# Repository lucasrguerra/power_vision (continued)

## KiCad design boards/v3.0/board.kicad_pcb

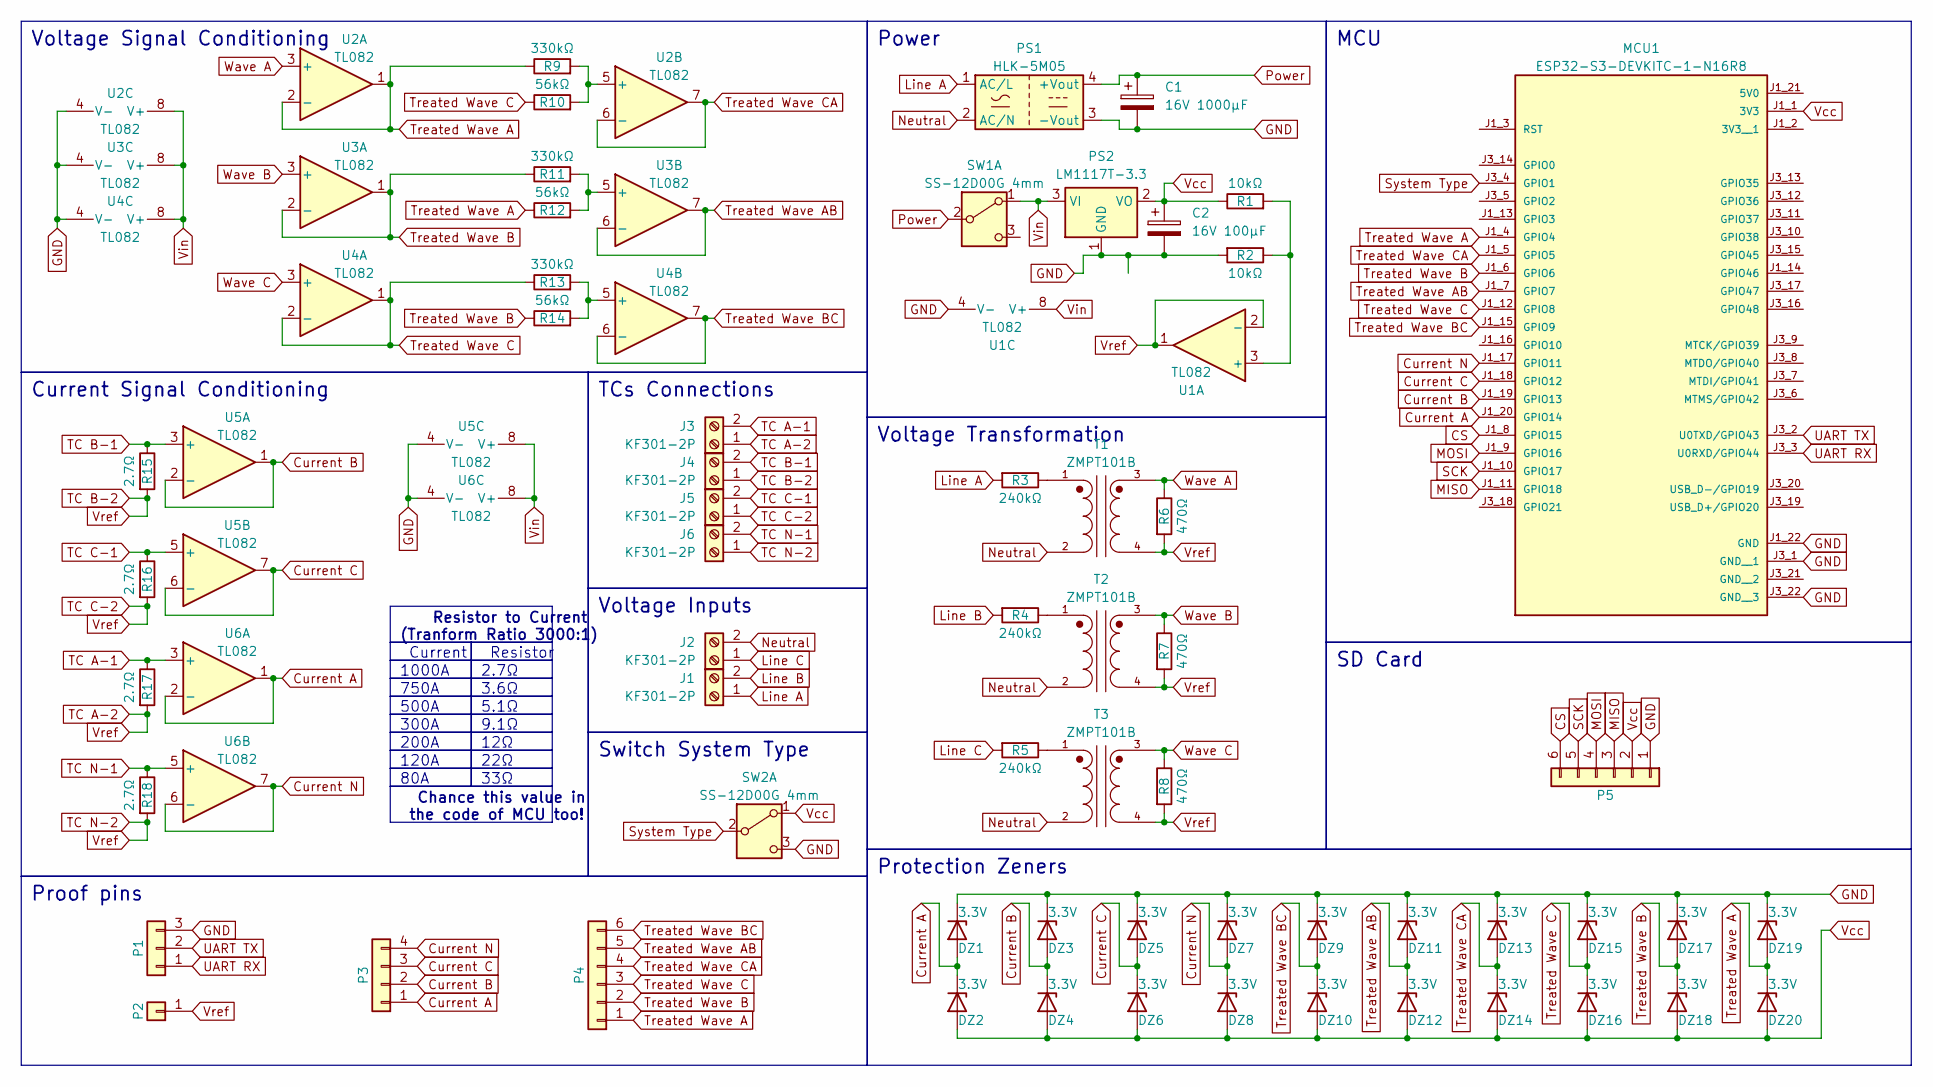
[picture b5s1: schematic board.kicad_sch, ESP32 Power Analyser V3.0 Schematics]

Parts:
C1: 16V 1000µF; CP_Radial_D6.3mm_P2.50mm
C2: 16V 100µF; CP_Radial_D5.0mm_P2.00mm
DZ1, DZ2, DZ3, DZ4, DZ5, DZ6, DZ7, DZ8, DZ9, DZ10, DZ11, DZ12, DZ13, DZ14, DZ15, DZ16, DZ17, DZ18, DZ19, DZ20: 3.3V; D_DO-34_SOD68_P7.62mm_Horizontal
J1, J2, J3, J4, J5, J6: KF301-2P; TerminalBlock_bornier-2_P5.08mm
MCU1: ESP32-S3-DEVKITC-1-N16R8; XCVR_ESP32-S3-DEVKITC-1-N8R2; PARTREV V1
P1: Pin Header; PinHeader_1x03_P2.54mm_Vertical
P2: Pin Header; PinHeader_1x01_P2.54mm_Vertical
P3: Pin Header; PinHeader_1x04_P2.54mm_Vertical
P4, P5: Pin Header; PinHeader_1x06_P2.54mm_Vertical
PS1: HLK-5M05; Converter_ACDC_HiLink_HLK-5Mxx
PS2: LM1117T-3.3; TO-220-3_Vertical
R1, R2: 10kΩ; R_Axial_DIN0207_L6.3mm_D2.5mm_P10.16mm_Horizontal
R3, R4, R5: 240kΩ; R_Axial_DIN0207_L6.3mm_D2.5mm_P10.16mm_Horizontal
R6, R7, R8: 470Ω; R_Axial_DIN0207_L6.3mm_D2.5mm_P10.16mm_Horizontal
R9, R11, R13: 330kΩ; R_Axial_DIN0207_L6.3mm_D2.5mm_P10.16mm_Horizontal
R10, R12, R14: 56kΩ; R_Axial_DIN0207_L6.3mm_D2.5mm_P10.16mm_Horizontal
R15, R16, R17, R18: 2.7Ω; R_Axial_DIN0207_L6.3mm_D2.5mm_P10.16mm_Horizontal
SW1, SW2: SS-12D00G 4mm; PinHeader_1x03_P2.54mm_Vertical
T1, T2, T3: ZMPT101B; XFMR_ZMPT101B; PARTREV NA
U1, U2, U3, U4, U5, U6: TL082; DIP-8_W7.62mm_Socket

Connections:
CS: MCU1.J1_8 (GPIO15), P5.6
Current A: DZ1.2 (A), DZ2.1 (K), MCU1.J1_20 (GPIO14), P3.1, U6.1, U6.2 (-)
Current B: DZ3.2 (A), DZ4.1 (K), MCU1.J1_19 (GPIO13), P3.2, U5.1, U5.2 (-)
Current C: DZ5.2 (A), DZ6.1 (K), MCU1.J1_18 (GPIO12), P3.3, U5.6 (-), U5.7
Current N: DZ7.2 (A), DZ8.1 (K), MCU1.J1_17 (GPIO11), P3.4, U6.6 (-), U6.7
GND: C1.2, C2.2, DZ1.1 (K), DZ3.1 (K), DZ5.1 (K), DZ7.1 (K), DZ9.1 (K), DZ11.1 (K), DZ13.1 (K), DZ15.1 (K), DZ17.1 (K), DZ19.1 (K), MCU1.J1_22 (GND), MCU1.J3_1 (GND__1), MCU1.J3_22 (GND__3), P1.3, P5.1, PS1.3 (-Vout), PS2.1 (GND), R2.2, SW2.3 (C), U1.4 (V-), U2.4 (V-), U3.4 (V-), U4.4 (V-), U5.4 (V-), U6.4 (V-)
Line A: J1.1, PS1.1 (AC/L), R3.2
Line B: J1.2, R4.2
Line C: J2.1, R5.2
MISO: MCU1.J1_11 (GPIO18), P5.3
MOSI: MCU1.J1_9 (GPIO16), P5.4
unnamed: R3.1, T1.1
unnamed: R4.1, T2.1
unnamed: R5.1, T3.1
unnamed: R1.2, R2.1, U1.3 (+)
unnamed: R9.2, R10.2, U2.5 (+)
unnamed: R11.2, R12.2, U3.5 (+)
unnamed: R13.2, R14.2, U4.5 (+)
Neutral: J2.2, PS1.2 (AC/N), T1.2, T2.2, T3.2
Power: C1.1, PS1.4 (+Vout), SW1.2 (B)
SCK: MCU1.J1_10 (GPIO17), P5.5
System Type: MCU1.J3_4 (GPIO1), SW2.2 (B)
TC A-1: J3.2, R17.1, U6.3 (+)
TC A-2: J3.1, J4.1, J5.1, J6.1, P2.1, R6.2, R7.2, R8.2, R15.2, R16.2, R17.2, R18.2, T1.4, T2.4, T3.4, U1.1, U1.2 (-)
TC B-1: J4.2, R15.1, U5.3 (+)
TC C-1: J5.2, R16.1, U5.5 (+)
TC N-1: J6.2, R18.1, U6.5 (+)
Treated Wave A: DZ19.2 (A), DZ20.1 (K), MCU1.J1_4 (GPIO4), P4.1, R9.1, R12.1, U2.1, U2.2 (-)
Treated Wave AB: DZ11.2 (A), DZ12.1 (K), MCU1.J1_7 (GPIO7), P4.5, U3.6 (-), U3.7
Treated Wave B: DZ17.2 (A), DZ18.1 (K), MCU1.J1_6 (GPIO6), P4.2, R11.1, R14.1, U3.1, U3.2 (-)
Treated Wave BC: DZ9.2 (A), DZ10.1 (K), MCU1.J1_15 (GPIO9), P4.6, U4.6 (-), U4.7
Treated Wave C: DZ15.2 (A), DZ16.1 (K), MCU1.J1_12 (GPIO8), P4.3, R10.1, R13.1, U4.1, U4.2 (-)
Treated Wave CA: DZ13.2 (A), DZ14.1 (K), MCU1.J1_5 (GPIO5), P4.4, U2.6 (-), U2.7
UART RX: MCU1.J3_3 (U0RXD/GPIO44), P1.1
UART TX: MCU1.J3_2 (U0TXD/GPIO43), P1.2
Vcc: C2.1, DZ2.2 (A), DZ4.2 (A), DZ6.2 (A), DZ8.2 (A), DZ10.2 (A), DZ12.2 (A), DZ14.2 (A), DZ16.2 (A), DZ18.2 (A), DZ20.2 (A), MCU1.J1_1 (3V3), P5.2, PS2.2 (VO), R1.1, SW2.1 (A)
Vin: PS2.3 (VI), SW1.1 (A), U1.8 (V+), U2.8 (V+), U3.8 (V+), U4.8 (V+), U5.8 (V+), U6.8 (V+)
Wave A: R6.1, T1.3, U2.3 (+)
Wave B: R7.1, T2.3, U3.3 (+)
Wave C: R8.1, T3.3, U4.3 (+)

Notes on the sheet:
33Ω
12Ω
500A
Chance this value in the code of MCU too!
Current
300A
MCU
3.6Ω
750A
5.1Ω
Power
Voltage Inputs
22Ω
9.1Ω
120A
Protection Zeners
Current Signal Conditioning
1000A
Voltage Transformation
200A
Switch System Type
80A
SD Card
Resistor
2.7Ω
Resistor to Current (Tranform Ratio 3000:1)
TCs Connections
Proof pins
Voltage Signal Conditioning

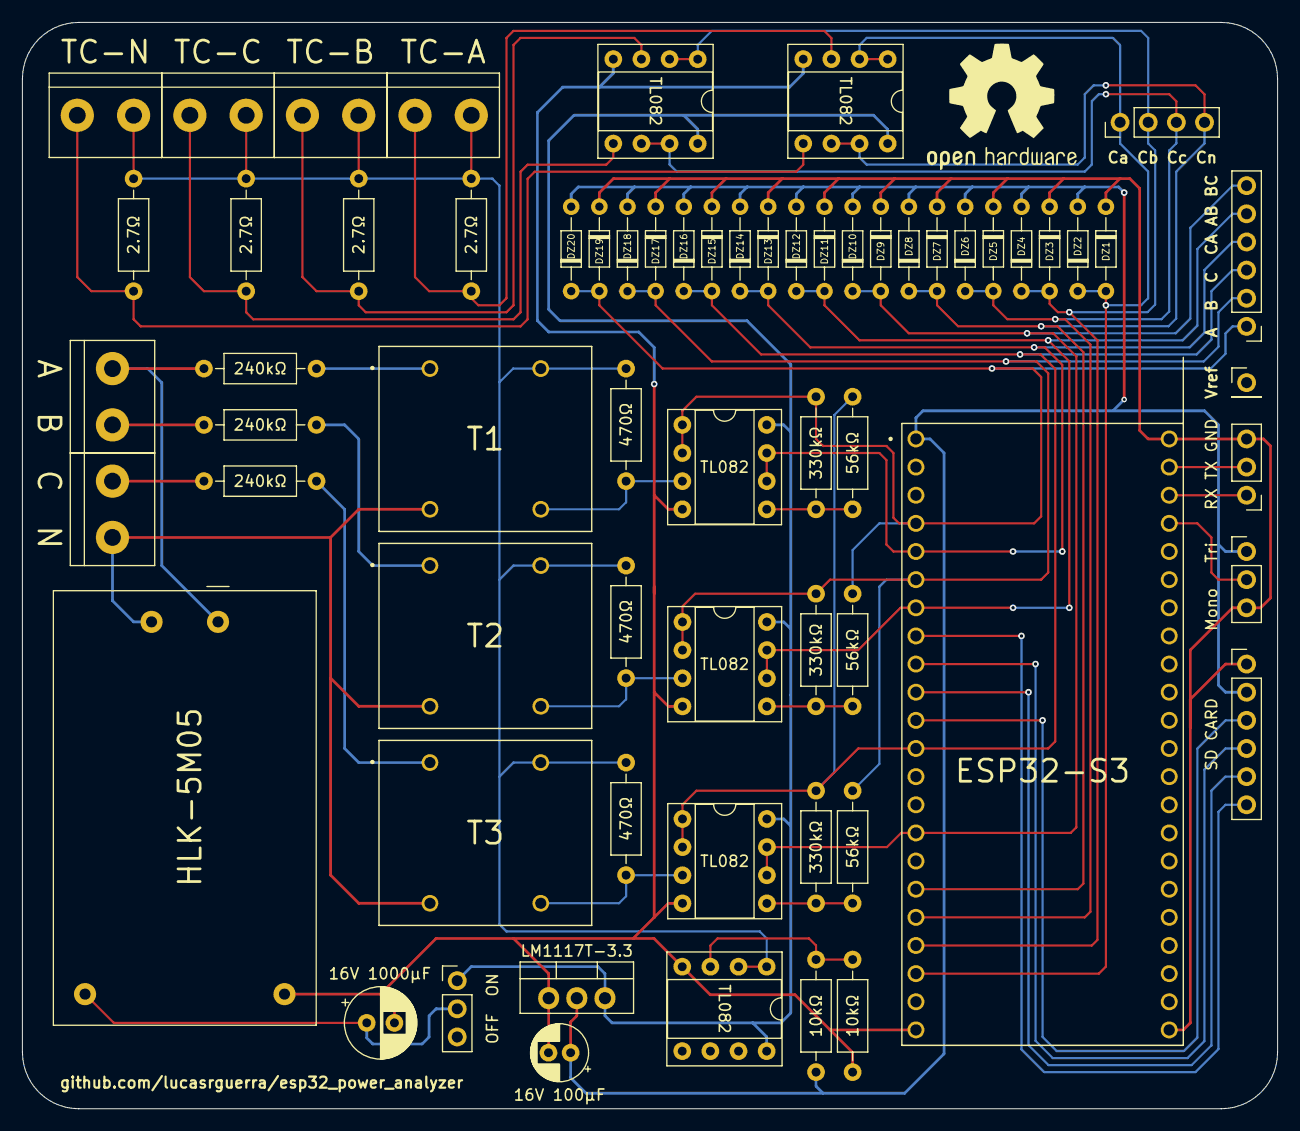
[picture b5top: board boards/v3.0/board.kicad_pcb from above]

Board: 2 copper layers, 113.3 x 98.0 mm, 65 parts (0 on the bottom side), 40 nets.

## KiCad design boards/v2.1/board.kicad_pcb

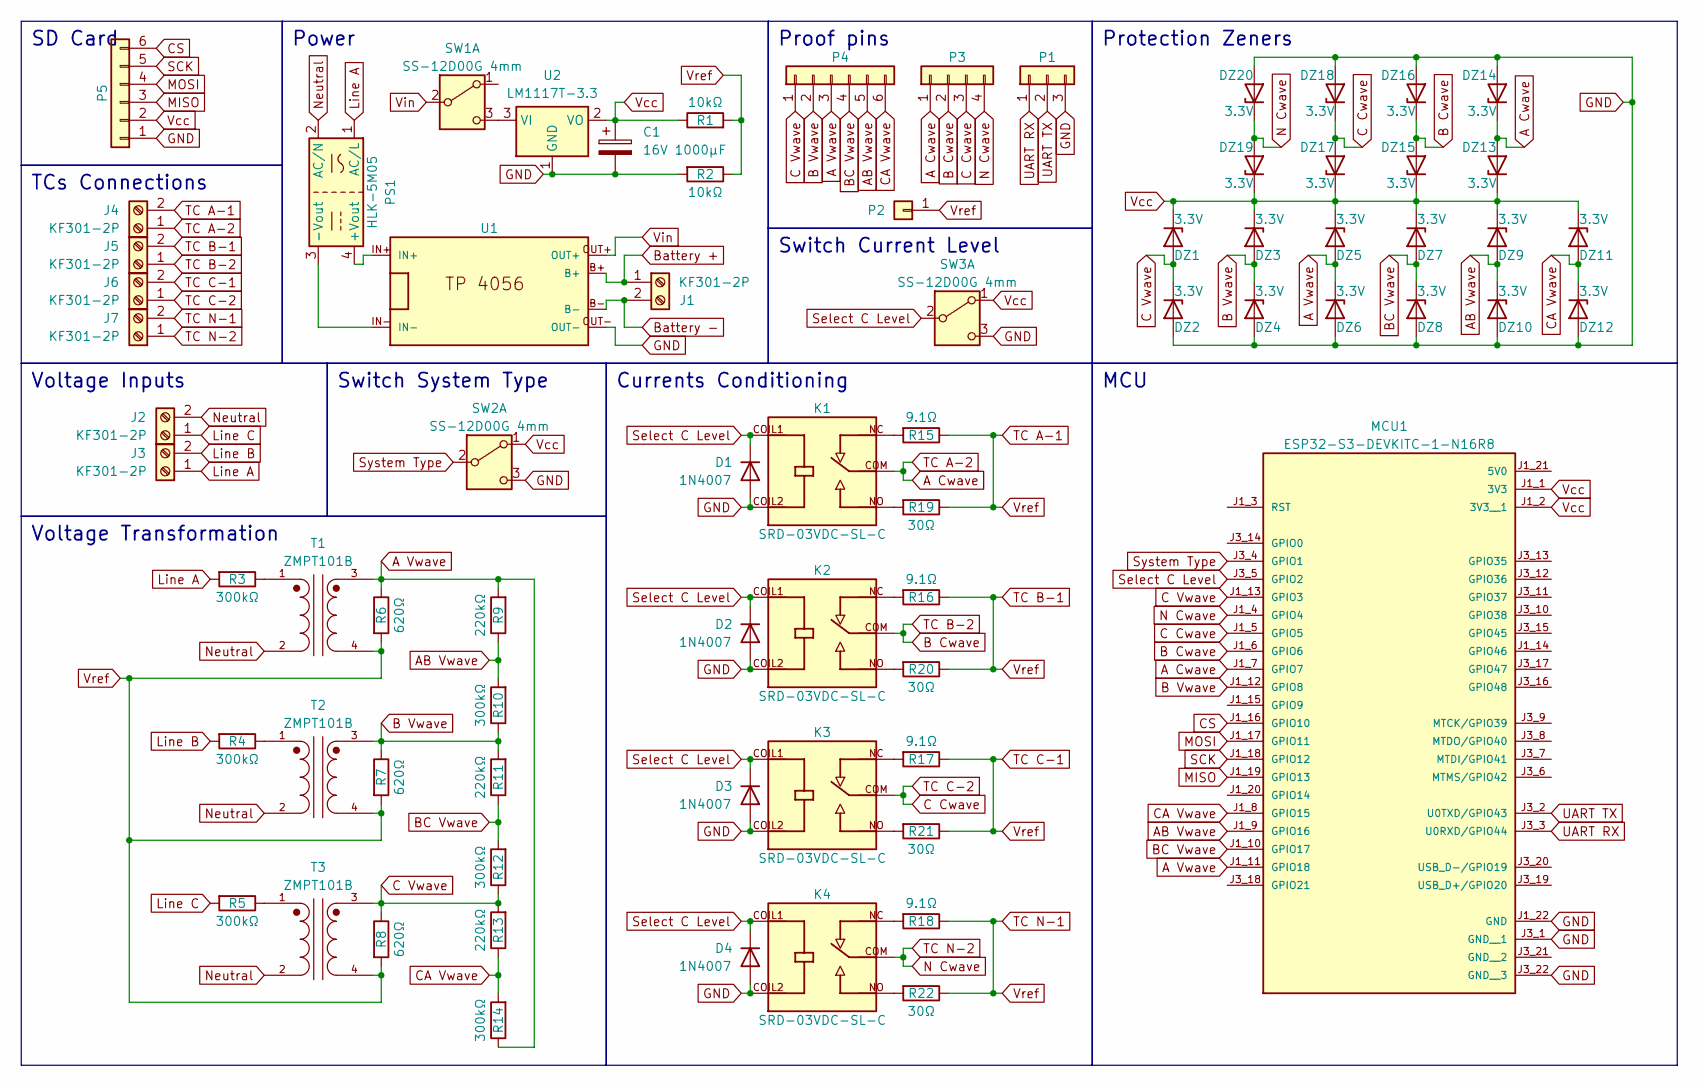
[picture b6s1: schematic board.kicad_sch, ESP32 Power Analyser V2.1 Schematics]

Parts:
C1: 16V 1000µF; CP_Radial_D6.3mm_P2.50mm
D1, D2, D3, D4: 1N4007; D_DO-41_SOD81_P10.16mm_Horizontal
DZ1, DZ2, DZ3, DZ4, DZ5, DZ6, DZ7, DZ8, DZ9, DZ10, DZ11, DZ12, DZ13, DZ14, DZ15, DZ16, DZ17, DZ18, DZ19, DZ20: 3.3V; D_DO-34_SOD68_P7.62mm_Horizontal
J1, J2, J3, J4, J5, J6, J7: KF301-2P; TerminalBlock_bornier-2_P5.08mm
K1, K2, K3, K4: SRD-03VDC-SL-C; RELAY_SRD-03VDC-SL-C; PARTREV 20161104
MCU1: ESP32-S3-DEVKITC-1-N16R8; XCVR_ESP32-S3-DEVKITC-1-N8R2; PARTREV V1
P1: Pin Header; PinHeader_1x03_P2.54mm_Vertical
P2: Pin Header; PinHeader_1x01_P2.54mm_Vertical
P3: Pin Header; PinHeader_1x04_P2.54mm_Vertical
P4, P5: Pin Header; PinHeader_1x06_P2.54mm_Vertical
PS1: HLK-5M05; Converter_ACDC_HiLink_HLK-5Mxx
R1, R2: 10kΩ; R_Axial_DIN0207_L6.3mm_D2.5mm_P10.16mm_Horizontal
R3, R4, R5, R10, R12, R14: 300kΩ; R_Axial_DIN0207_L6.3mm_D2.5mm_P10.16mm_Horizontal
R6, R7, R8: 620Ω; R_Axial_DIN0207_L6.3mm_D2.5mm_P10.16mm_Horizontal
R9, R11, R13: 220kΩ; R_Axial_DIN0207_L6.3mm_D2.5mm_P10.16mm_Horizontal
R15, R16, R17, R18: 9.1Ω; R_Axial_DIN0207_L6.3mm_D2.5mm_P10.16mm_Horizontal
R19, R20, R21, R22: 30Ω; R_Axial_DIN0207_L6.3mm_D2.5mm_P10.16mm_Horizontal
SW1, SW2, SW3: SS-12D00G 4mm; PinHeader_1x03_P2.54mm_Vertical
T1, T2, T3: ZMPT101B; XFMR_ZMPT101B; PARTREV NA
U1: TP4056
U2: LM1117T-3.3; TO-220-3_Vertical

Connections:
A Cwave: DZ13.2 (A), DZ14.1 (K), J4.1, K1.COM, MCU1.J1_7 (GPIO7), P3.1
A Vwave: DZ5.2 (A), DZ6.1 (K), MCU1.J1_11 (GPIO18), P4.3, R6.1, R9.2, R14.1, T1.3
AB Vwave: DZ9.2 (A), DZ10.1 (K), MCU1.J1_9 (GPIO16), P4.5, R9.1, R10.2
B Cwave: DZ15.2 (A), DZ16.1 (K), J5.1, K2.COM, MCU1.J1_6 (GPIO6), P3.2
B Vwave: DZ3.2 (A), DZ4.1 (K), MCU1.J1_12 (GPIO8), P4.2, R7.1, R10.1, R11.2, T2.3
BC Vwave: DZ7.2 (A), DZ8.1 (K), MCU1.J1_10 (GPIO17), P4.4, R11.1, R12.2
Battery +: J1.1, U1.B+
Battery -: J1.2, U1.B-
C Cwave: DZ17.2 (A), DZ18.1 (K), J6.1, K3.COM, MCU1.J1_5 (GPIO5), P3.3
C Vwave: DZ1.2 (A), DZ2.1 (K), MCU1.J1_13 (GPIO3), P4.1, R8.1, R12.1, R13.2, T3.3
CA Vwave: DZ11.2 (A), DZ12.1 (K), MCU1.J1_8 (GPIO15), P4.6, R13.1, R14.2
CS: MCU1.J1_16 (GPIO10), P5.6
GND: C1.2, D1.2 (A), D2.2 (A), D3.2 (A), D4.2 (A), DZ2.2 (A), DZ4.2 (A), DZ6.2 (A), DZ8.2 (A), DZ10.2 (A), DZ12.2 (A), DZ14.2 (A), DZ16.2 (A), DZ18.2 (A), DZ20.2 (A), K1.COIL2, K2.COIL2, K3.COIL2, K4.COIL2, MCU1.J1_22 (GND), MCU1.J3_1 (GND__1), MCU1.J3_22 (GND__3), P1.3, P5.1, R2.2, SW2.3 (C), SW3.3 (C), U1.OUT-, U2.1 (GND)
Line A: J3.1, PS1.1 (AC/L), R3.2
Line B: J3.2, R4.2
Line C: J2.1, R5.2
MISO: MCU1.J1_19 (GPIO13), P5.3
MOSI: MCU1.J1_17 (GPIO11), P5.4
N Cwave: DZ19.2 (A), DZ20.1 (K), J7.1, K4.COM, MCU1.J1_4 (GPIO4), P3.4
unnamed: K1.NC, R15.2
unnamed: K1.NO, R19.2
unnamed: K2.NC, R16.2
unnamed: K2.NO, R20.2
unnamed: K3.NC, R17.2
unnamed: K3.NO, R21.2
unnamed: K4.NC, R18.2
unnamed: K4.NO, R22.2
unnamed: PS1.4 (+Vout), U1.IN+
unnamed: PS1.3 (-Vout), U1.IN-
unnamed: R3.1, T1.1
unnamed: R4.1, T2.1
unnamed: R5.1, T3.1
unnamed: SW1.3 (C), U2.3 (VI)
Neutral: J2.2, PS1.2 (AC/N), T1.2, T2.2, T3.2
SCK: MCU1.J1_18 (GPIO12), P5.5
Select C Level: D1.1 (K), D2.1 (K), D3.1 (K), D4.1 (K), K1.COIL1, K2.COIL1, K3.COIL1, K4.COIL1, MCU1.J3_5 (GPIO2), SW3.2 (B)
System Type: MCU1.J3_4 (GPIO1), SW2.2 (B)
TC A-1: J4.2, J5.2, J6.2, J7.2, P2.1, R1.2, R2.1, R6.2, R7.2, R8.2, R15.1, R16.1, R17.1, R18.1, R19.1, R20.1, R21.1, R22.1, T1.4, T2.4, T3.4
UART RX: MCU1.J3_3 (U0RXD/GPIO44), P1.1
UART TX: MCU1.J3_2 (U0TXD/GPIO43), P1.2
Vcc: C1.1, DZ1.1 (K), DZ3.1 (K), DZ5.1 (K), DZ7.1 (K), DZ9.1 (K), DZ11.1 (K), DZ13.1 (K), DZ15.1 (K), DZ17.1 (K), DZ19.1 (K), MCU1.J1_1 (3V3), MCU1.J1_2 (3V3__1), P5.2, R1.1, SW2.1 (A), SW3.1 (A), U2.2 (VO)
Vin: SW1.2 (B), U1.OUT+

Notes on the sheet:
Switch Current Level
MCU
Power
Voltage Inputs
Protection Zeners
Voltage Transformation
Switch System Type
SD Card
TCs Connections
Proof pins
Currents Conditioning

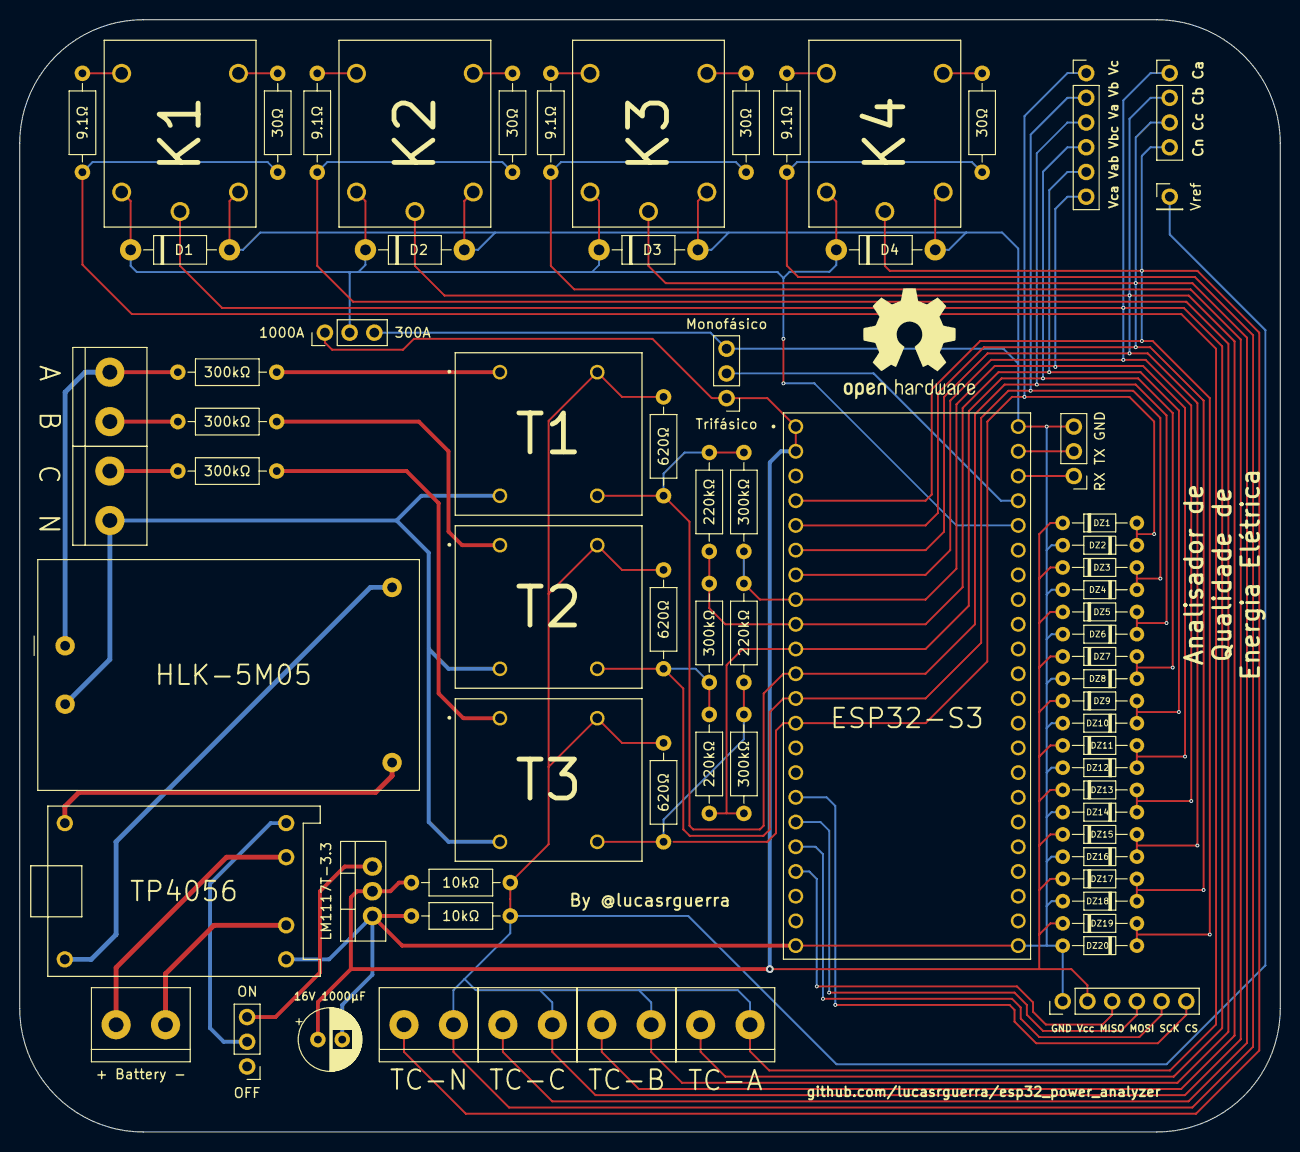
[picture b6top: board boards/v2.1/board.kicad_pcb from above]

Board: 2 copper layers, 129.5 x 114.3 mm, 73 parts (0 on the bottom side), 42 nets.

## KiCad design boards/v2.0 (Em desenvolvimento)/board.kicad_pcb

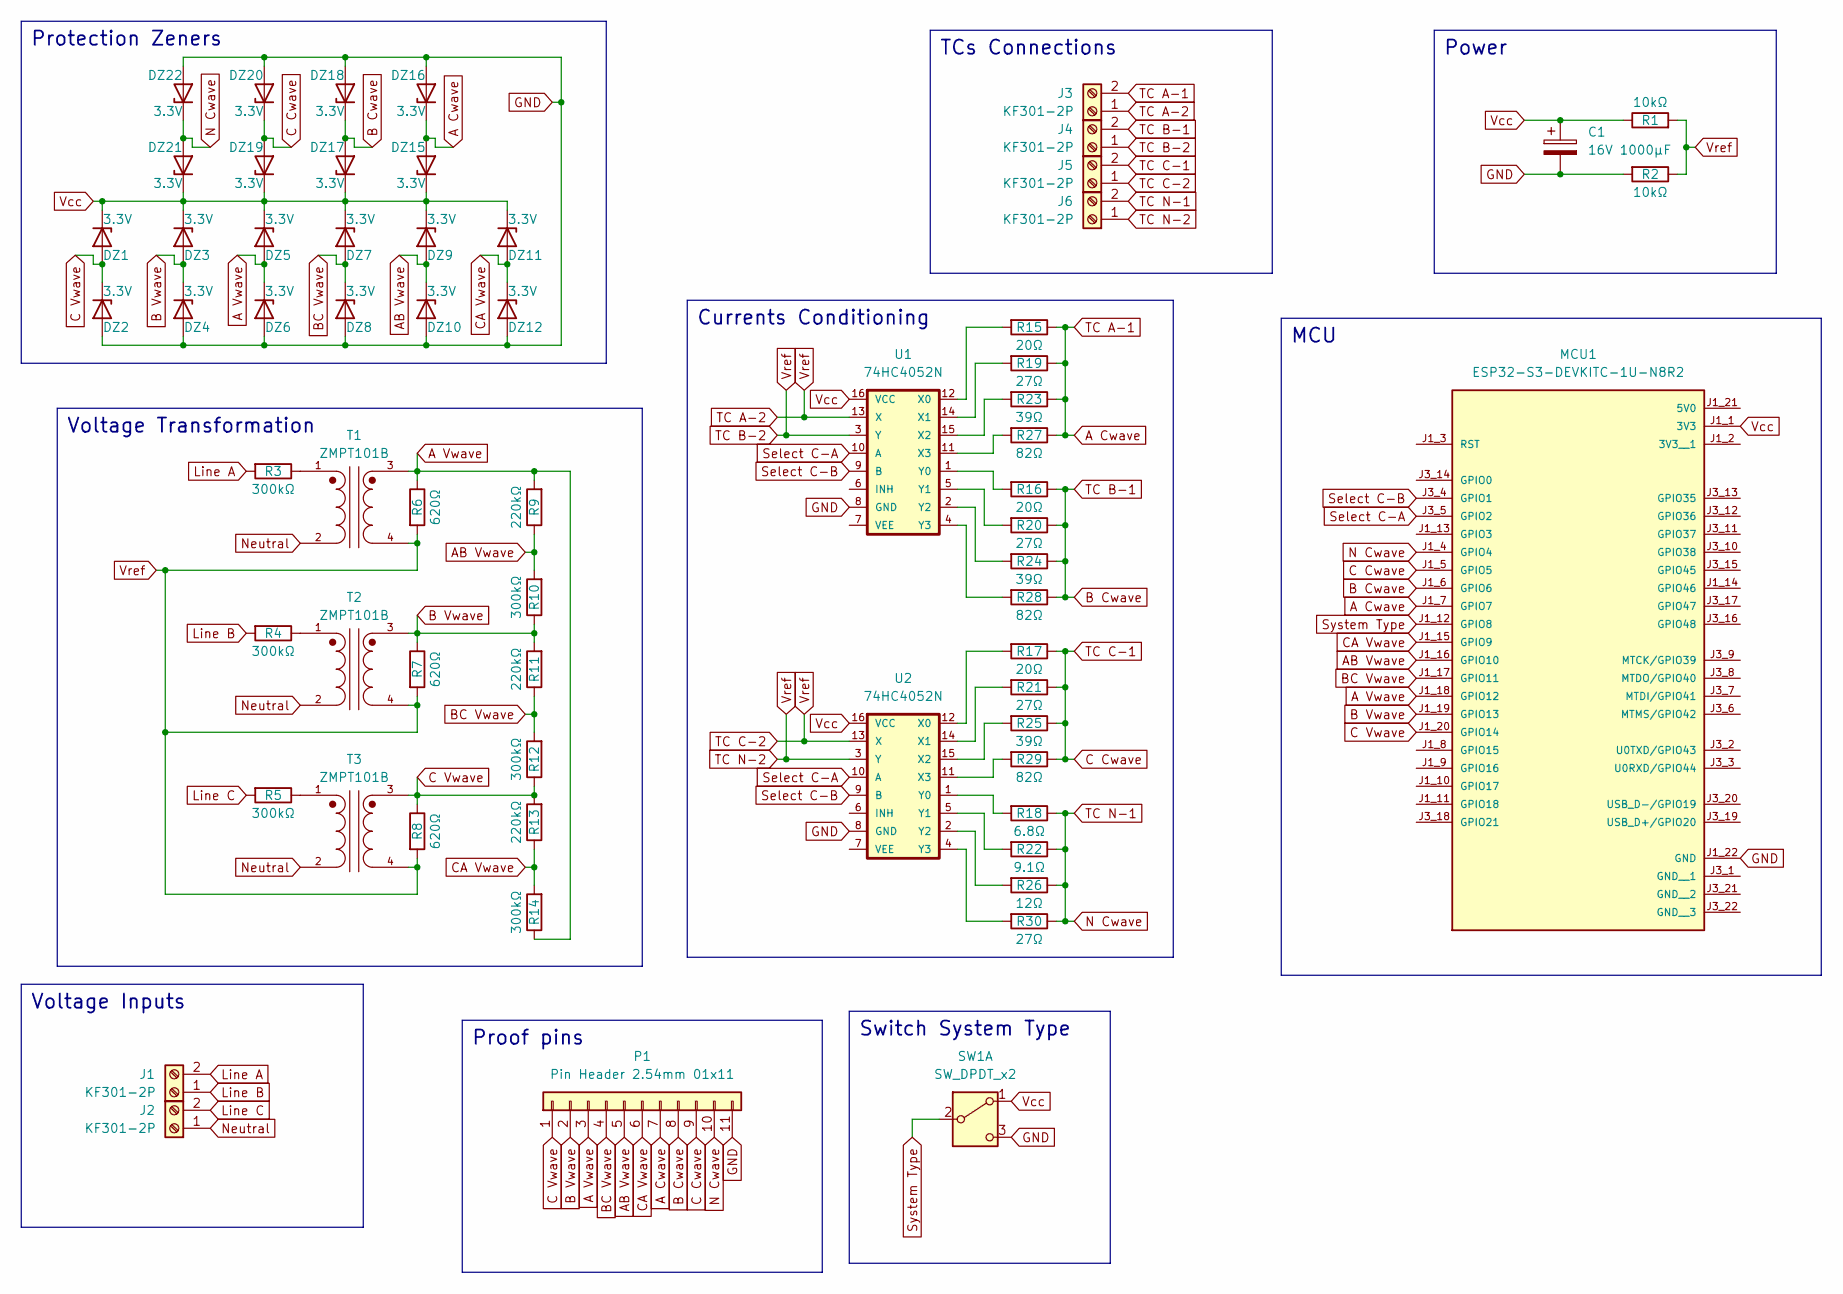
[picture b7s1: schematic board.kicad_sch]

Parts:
C1: 16V 1000µF; CP_Radial_D6.3mm_P2.50mm
DZ1, DZ2, DZ3, DZ4, DZ5, DZ6, DZ7, DZ8, DZ9, DZ10, DZ11, DZ12, DZ15, DZ16, DZ17, DZ18, DZ19, DZ20, DZ21, DZ22: 3.3V; D_DO-34_SOD68_P7.62mm_Horizontal
J1, J2, J3, J4, J5, J6: KF301-2P; TerminalBlock_bornier-2_P5.08mm
MCU1: ESP32-S3-DEVKITC-1U-N8R2; XCVR_ESP32-S3-DEVKITC-1U-N8R2; PARTREV 5.3
P1: Pin Header 2.54mm 01x11; PinHeader_1x11_P2.54mm_Vertical
R1, R2: 10kΩ; R_Axial_DIN0207_L6.3mm_D2.5mm_P10.16mm_Horizontal
R3, R4, R5, R10, R12, R14: 300kΩ; R_Axial_DIN0207_L6.3mm_D2.5mm_P10.16mm_Horizontal
R6, R7, R8: 620Ω; R_Axial_DIN0207_L6.3mm_D2.5mm_P10.16mm_Horizontal
R9, R11, R13: 220kΩ; R_Axial_DIN0207_L6.3mm_D2.5mm_P10.16mm_Horizontal
R15, R16, R17: 20Ω; R_Axial_DIN0207_L6.3mm_D2.5mm_P10.16mm_Horizontal
R18: 6.8Ω; R_Axial_DIN0207_L6.3mm_D2.5mm_P10.16mm_Horizontal
R19, R20, R21, R30: 27Ω; R_Axial_DIN0207_L6.3mm_D2.5mm_P10.16mm_Horizontal
R22: 9.1Ω; R_Axial_DIN0207_L6.3mm_D2.5mm_P10.16mm_Horizontal
R23, R24, R25: 39Ω; R_Axial_DIN0207_L6.3mm_D2.5mm_P10.16mm_Horizontal
R26: 12Ω; R_Axial_DIN0207_L6.3mm_D2.5mm_P10.16mm_Horizontal
R27, R28, R29: 82Ω; R_Axial_DIN0207_L6.3mm_D2.5mm_P10.16mm_Horizontal
SW1: SW_DPDT_x2; PinHeader_1x03_P2.54mm_Vertical
T1, T2, T3: ZMPT101B; XFMR_ZMPT101B; PARTREV NA
U1, U2: 74HC4052N; DIL16

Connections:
A Cwave: DZ15.2 (A), DZ16.1 (K), J3.2, MCU1.J1_7 (GPIO7), P1.7, R15.1, R19.1, R23.1, R27.1
A Vwave: DZ5.2 (A), DZ6.1 (K), MCU1.J1_18 (GPIO12), P1.3, R6.1, R9.2, R14.1, T1.3
AB Vwave: DZ9.2 (A), DZ10.1 (K), MCU1.J1_16 (GPIO10), P1.5, R9.1, R10.2
B Cwave: DZ17.2 (A), DZ18.1 (K), J4.2, MCU1.J1_6 (GPIO6), P1.8, R16.1, R20.1, R24.1, R28.1
B Vwave: DZ3.2 (A), DZ4.1 (K), MCU1.J1_19 (GPIO13), P1.2, R7.1, R10.1, R11.2, T2.3
BC Vwave: DZ7.2 (A), DZ8.1 (K), MCU1.J1_17 (GPIO11), P1.4, R11.1, R12.2
C Cwave: DZ19.2 (A), DZ20.1 (K), J5.2, MCU1.J1_5 (GPIO5), P1.9, R17.1, R21.1, R25.1, R29.1
C Vwave: DZ1.2 (A), DZ2.1 (K), MCU1.J1_20 (GPIO14), P1.1, R8.1, R12.1, R13.2, T3.3
CA Vwave: DZ11.2 (A), DZ12.1 (K), MCU1.J1_15 (GPIO9), P1.6, R13.1, R14.2
GND: C1.2, DZ2.2 (A), DZ4.2 (A), DZ6.2 (A), DZ8.2 (A), DZ10.2 (A), DZ12.2 (A), DZ16.2 (A), DZ18.2 (A), DZ20.2 (A), DZ22.2 (A), MCU1.J1_22 (GND), P1.11, R2.2, SW1.3 (C), U1.8 (GND), U2.8 (GND)
Line A: J1.2, R3.2
Line B: J1.1, R4.2
Line C: J2.2, R5.2
N Cwave: DZ21.2 (A), DZ22.1 (K), J6.2, MCU1.J1_4 (GPIO4), P1.10, R18.1, R22.1, R26.1, R30.1
unnamed: R3.1, T1.1
unnamed: R4.1, T2.1
unnamed: R5.1, T3.1
unnamed: R15.2, U1.12 (X0)
unnamed: R19.2, U1.14 (X1)
unnamed: R23.2, U1.15 (X2)
unnamed: R27.2, U1.11 (X3)
unnamed: R16.2, U1.1 (Y0)
unnamed: R20.2, U1.5 (Y1)
unnamed: R24.2, U1.2 (Y2)
unnamed: R28.2, U1.4 (Y3)
unnamed: R17.2, U2.12 (X0)
unnamed: R21.2, U2.14 (X1)
unnamed: R25.2, U2.15 (X2)
unnamed: R29.2, U2.11 (X3)
unnamed: R18.2, U2.1 (Y0)
unnamed: R22.2, U2.5 (Y1)
unnamed: R26.2, U2.2 (Y2)
unnamed: R30.2, U2.4 (Y3)
Neutral: J2.1, T1.2, T2.2, T3.2
Select C-A: MCU1.J3_5 (GPIO2), U1.10 (A), U2.10 (A)
Select C-B: MCU1.J3_4 (GPIO1), U1.9 (B), U2.9 (B)
System Type: MCU1.J1_12 (GPIO8), SW1.2 (B)
TC A-2: J3.1, J4.1, J5.1, J6.1, R1.2, R2.1, R6.2, R7.2, R8.2, T1.4, T2.4, T3.4, U1.3 (Y), U1.13 (X), U2.3 (Y), U2.13 (X)
Vcc: C1.1, DZ1.1 (K), DZ3.1 (K), DZ5.1 (K), DZ7.1 (K), DZ9.1 (K), DZ11.1 (K), DZ15.1 (K), DZ17.1 (K), DZ19.1 (K), DZ21.1 (K), MCU1.J1_1 (3V3), R1.1, SW1.1 (A), U1.16 (VCC), U2.16 (VCC)

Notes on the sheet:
MCU
Power
Voltage Inputs
Protection Zeners
Voltage Transformation
Switch System Type
TCs Connections
Proof pins
Currents Conditioning

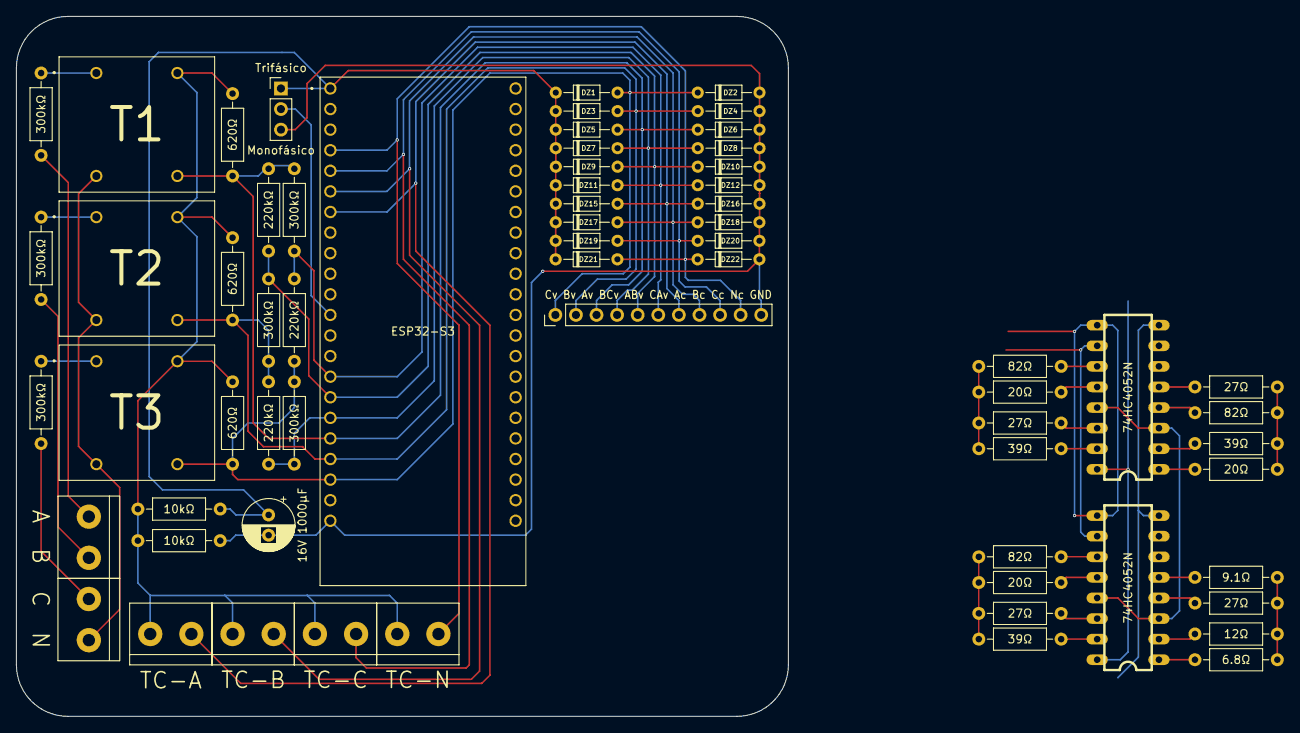
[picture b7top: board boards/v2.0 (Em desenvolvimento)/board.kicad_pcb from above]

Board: 2 copper layers, 95.2 x 86.4 mm, 65 parts (0 on the bottom side), 39 nets.

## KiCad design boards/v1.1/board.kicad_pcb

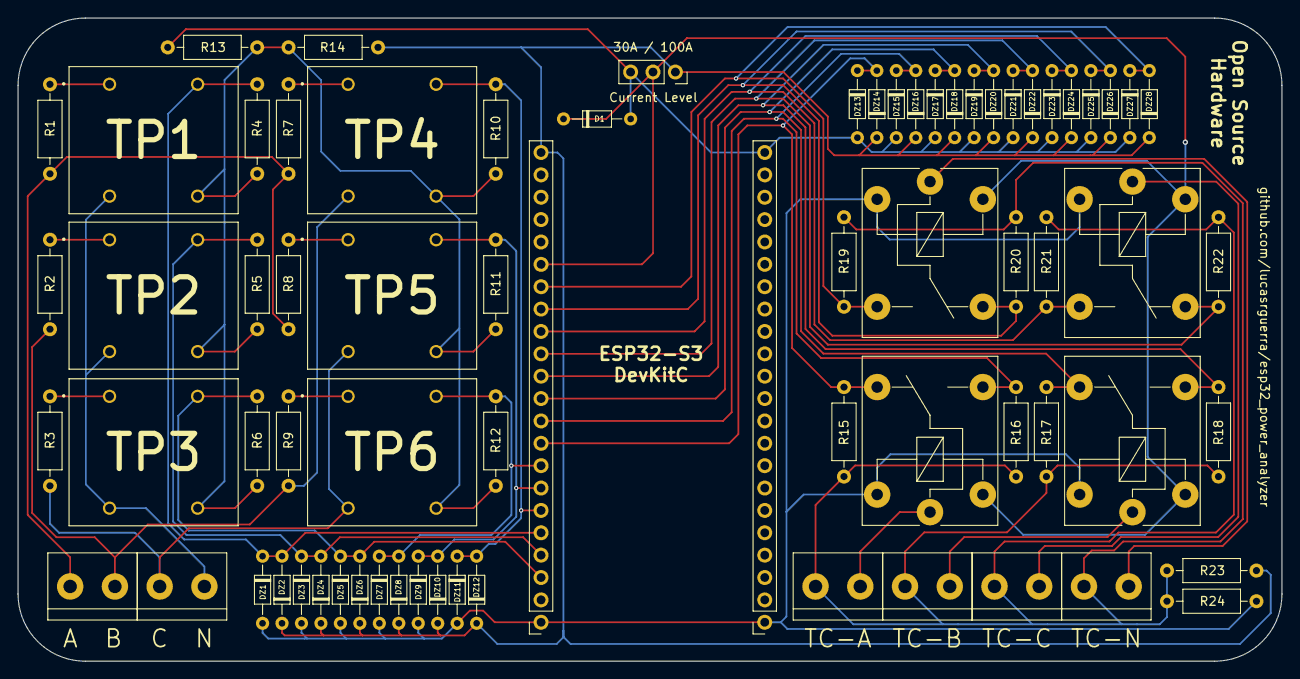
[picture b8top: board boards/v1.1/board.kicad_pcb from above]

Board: 2 copper layers, 143.5 x 73.0 mm, 72 parts (0 on the bottom side), 33 nets.

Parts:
D1: 1N4007; D_DO-34_SOD68_P7.62mm_Horizontal
DZ1, DZ2, DZ3, DZ4, DZ5, DZ6, DZ7, DZ8, DZ9, DZ10, DZ11, DZ12, DZ13, DZ14, DZ15, DZ16, DZ17, DZ18, DZ19, DZ20, DZ21, DZ22, DZ23, DZ24, DZ25, DZ26, DZ27, DZ28: 3.3v; D_DO-34_SOD68_P7.62mm_Horizontal
ESP32-S3_BACK1, ESP32-S3_FRONT1: Conn_01x22_Socket; PinSocket_1x22_P2.54mm_Vertical
K1, K1#2, K1#3, K1#4: FINDER-36.11; Relay_SPDT_Finder_36.11
R1, R2, R3, R4, R5, R6, R7, R8, R9, R10, R11, R12, R13, R14, R15, R16, R17, R18, R19, R20, R21, R22, R23, R24: R_Axial_DIN0207_L6.3mm_D2.5mm_P10.16mm_Horizontal
ST1, ST1#2, ST1#3, ST1#4, ST1#5, ST2: WJ127-5.0-2P; TerminalBlock_bornier-2_P5.08mm
SW1: TerminalBlock_bornier-2_P5.08mm; PinSocket_1x03_P2.54mm_Vertical
TP1, TP2, TP3, TP4, TP5, TP6: ZMPT101B; XFMR_ZMPT101B

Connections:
Current_A: K1.11, ST1#4.2
Current_A_30A: DZ15.1 (K), DZ16.2 (A), ESP32-S3_FRONT1.10, K1.14, R16.1
Current_A_100A: DZ13.1 (K), DZ14.2 (A), ESP32-S3_FRONT1.9, K1.12, R15.1
Current_B: K1#2.11, ST1#5.2
Current_B_30A: DZ19.1 (K), DZ20.2 (A), ESP32-S3_FRONT1.12, K1#2.14, R18.1
Current_B_100A: DZ17.1 (K), DZ18.2 (A), ESP32-S3_FRONT1.11, K1#2.12, R17.1
Current_C: K1#3.11, ST1#2.2
Current_C_30A: DZ23.1 (K), DZ24.2 (A), ESP32-S3_FRONT1.14, K1#3.14, R21.1
Current_C_100A: DZ21.1 (K), DZ22.2 (A), ESP32-S3_FRONT1.13, K1#3.12, R22.1
Current_N: K1#4.11, ST1#3.2
Current_N_90A: DZ27.1 (K), DZ28.2 (A), ESP32-S3_FRONT1.16, K1#4.14, R19.1
Current_N_300A: DZ25.1 (K), DZ26.2 (A), ESP32-S3_FRONT1.15, K1#4.12, R20.1
GND: D1.2 (A), DZ1.2 (A), DZ3.2 (A), DZ5.2 (A), DZ7.2 (A), DZ9.2 (A), DZ11.2 (A), DZ13.2 (A), DZ15.2 (A), DZ17.2 (A), DZ19.2 (A), DZ21.2 (A), DZ23.2 (A), DZ25.2 (A), DZ27.2 (A), ESP32-S3_BACK1.1, ESP32-S3_BACK1.22, ESP32-S3_FRONT1.1, K1.A2, K1#2.A2, K1#3.A1, K1#4.A1, R13.1, R24.2, SW1.3 (C)
Line_A: R1.1, R7.1, R8.1, ST1.1
Line_AB_Load: R7.2, TP4.1
Line_AB_Wave: DZ11.1 (K), DZ12.2 (A), ESP32-S3_FRONT1.6, R10.2, TP4.4
Line_AC_Load: R8.2, TP5.1
Line_AC_Wave: DZ9.1 (K), DZ10.2 (A), ESP32-S3_FRONT1.7, R11.2, TP5.4
Line_A_Load: R1.2, TP1.1
Line_A_Wave: DZ1.1 (K), DZ2.2 (A), ESP32-S3_FRONT1.5, R4.2, TP1.4
Line_B: R2.1, R9.1, ST1.2, TP4.2
Line_BC_Load: R9.2, TP6.1
Line_BC_Wave: DZ7.1 (K), DZ8.2 (A), ESP32-S3_FRONT1.8, R12.2, TP6.4
Line_B_Load: R2.2, TP2.1
Line_B_Wave: DZ3.1 (K), DZ4.2 (A), ESP32-S3_FRONT1.4, R5.2, TP2.4
Line_C: R3.1, ST2.1, TP5.2, TP6.2
Line_C_Load: R3.2, TP3.1
Line_C_Wave: DZ5.1 (K), DZ6.2 (A), ESP32-S3_FRONT1.3, R6.2, TP3.4
Neutral: ST2.2, TP1.2, TP2.2, TP3.2
Select_Current: D1.1 (K), ESP32-S3_FRONT1.17, K1.A1, K1#2.A1, K1#3.A2, K1#4.A2, SW1.2 (B)
VCC: DZ2.1 (K), DZ4.1 (K), DZ6.1 (K), DZ8.1 (K), DZ10.1 (K), DZ12.1 (K), DZ14.1 (K), DZ16.1 (K), DZ18.1 (K), DZ20.1 (K), DZ22.1 (K), DZ24.1 (K), DZ26.1 (K), DZ28.1 (K), ESP32-S3_FRONT1.22, R14.1, R23.2, SW1.1 (A)
V_Ref_Current: R15.2, R16.2, R17.2, R18.2, R19.2, R20.2, R21.2, R22.2, R23.1, R24.1, ST1#2.1, ST1#3.1, ST1#4.1, ST1#5.1
V_Ref_Voltage: R4.1, R5.1, R6.1, R10.1, R11.1, R12.1, R13.2, R14.2, TP1.3, TP2.3, TP3.3, TP4.3, TP5.3, TP6.3

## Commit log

2024-02-01 Primeira parte
2024-02-16 Update algorithms to power analysis and create an base MCU code to ESP32-S3
2024-02-16 Create documents of project
2024-02-17 Update in calcs and docs
2024-03-01 Calculate the true rms voltage with ESP32-S3 DevKitC
2024-03-08 Update of boards
2024-03-08 Nova versão da placa
2024-03-08 Agradecimentos
2024-03-11 Correção das imagens nos READMEs
2024-03-12 Começo do desenvolvimento da placa v2.0
2024-03-25 Início do desenvolvimento da placa V2.0
2024-04-01 New version of board
2024-04-01 Update documents
2024-04-05 Atualização da placa V2.1
2024-04-29 Update code
2024-05-02 Finish of board v3.0 development and code update
2024-05-04 Revision of the v3.0 board
2024-05-04 Reduction in the size of v3.0 board
2024-05-04 Documentation update
2024-05-04 Update list of components
2024-05-04 Update in the list of components
2024-05-04 Simulation and documentation update
2024-05-04 Revision in the v3.0 board
2024-05-04 Update images
2024-05-08 Atualização na documentação
2024-05-12 Update firmware and boards
2024-05-12 Update the documents
2024-05-27 update all parts of project
2024-05-27 Update general documentation
2024-06-01 The last board and documentation update
2024-06-01 Update the list of components and calcs
2024-06-02 Add the earth plan in the v3.3 board
2024-06-02 Recalculation of load resistors
2024-06-03 Correction on the board v3.3 silkscreen
2024-06-04 Update calcs of resistors
2024-06-04 Update and correct calcs of the signals
2024-06-04 Update the simulation
2024-06-27 General Update
2024-06-27 Board IDs Correction and update documentation
2024-07-03 Initial tests of microcontroller code
2024-07-09 Initial tests of board
2024-07-09 Tests and results
2024-07-12 Web App interface
2024-07-12 Path correction
2024-07-12 Path web correction
2024-07-12 Directory correction
2024-07-12 Directory final correction
2024-07-12 Update the Web Application and Device WiFi Settings
2024-07-18 Code update
2024-09-28 Start V5.0 development
2024-09-28 Update board v5.0 docs
2024-09-29 Update in the V5 board
2025-05-09 Add Jupyter notebook for calculating possible sample rates
    - Introduced a new notebook `possible_sample_rates.ipynb` that calculates sample rates based on a base frequency of 60Hz.
    - The notebook iterates through a range of values to compute and print sample rates, frequencies, microseconds, and remainders for specific conditions.
